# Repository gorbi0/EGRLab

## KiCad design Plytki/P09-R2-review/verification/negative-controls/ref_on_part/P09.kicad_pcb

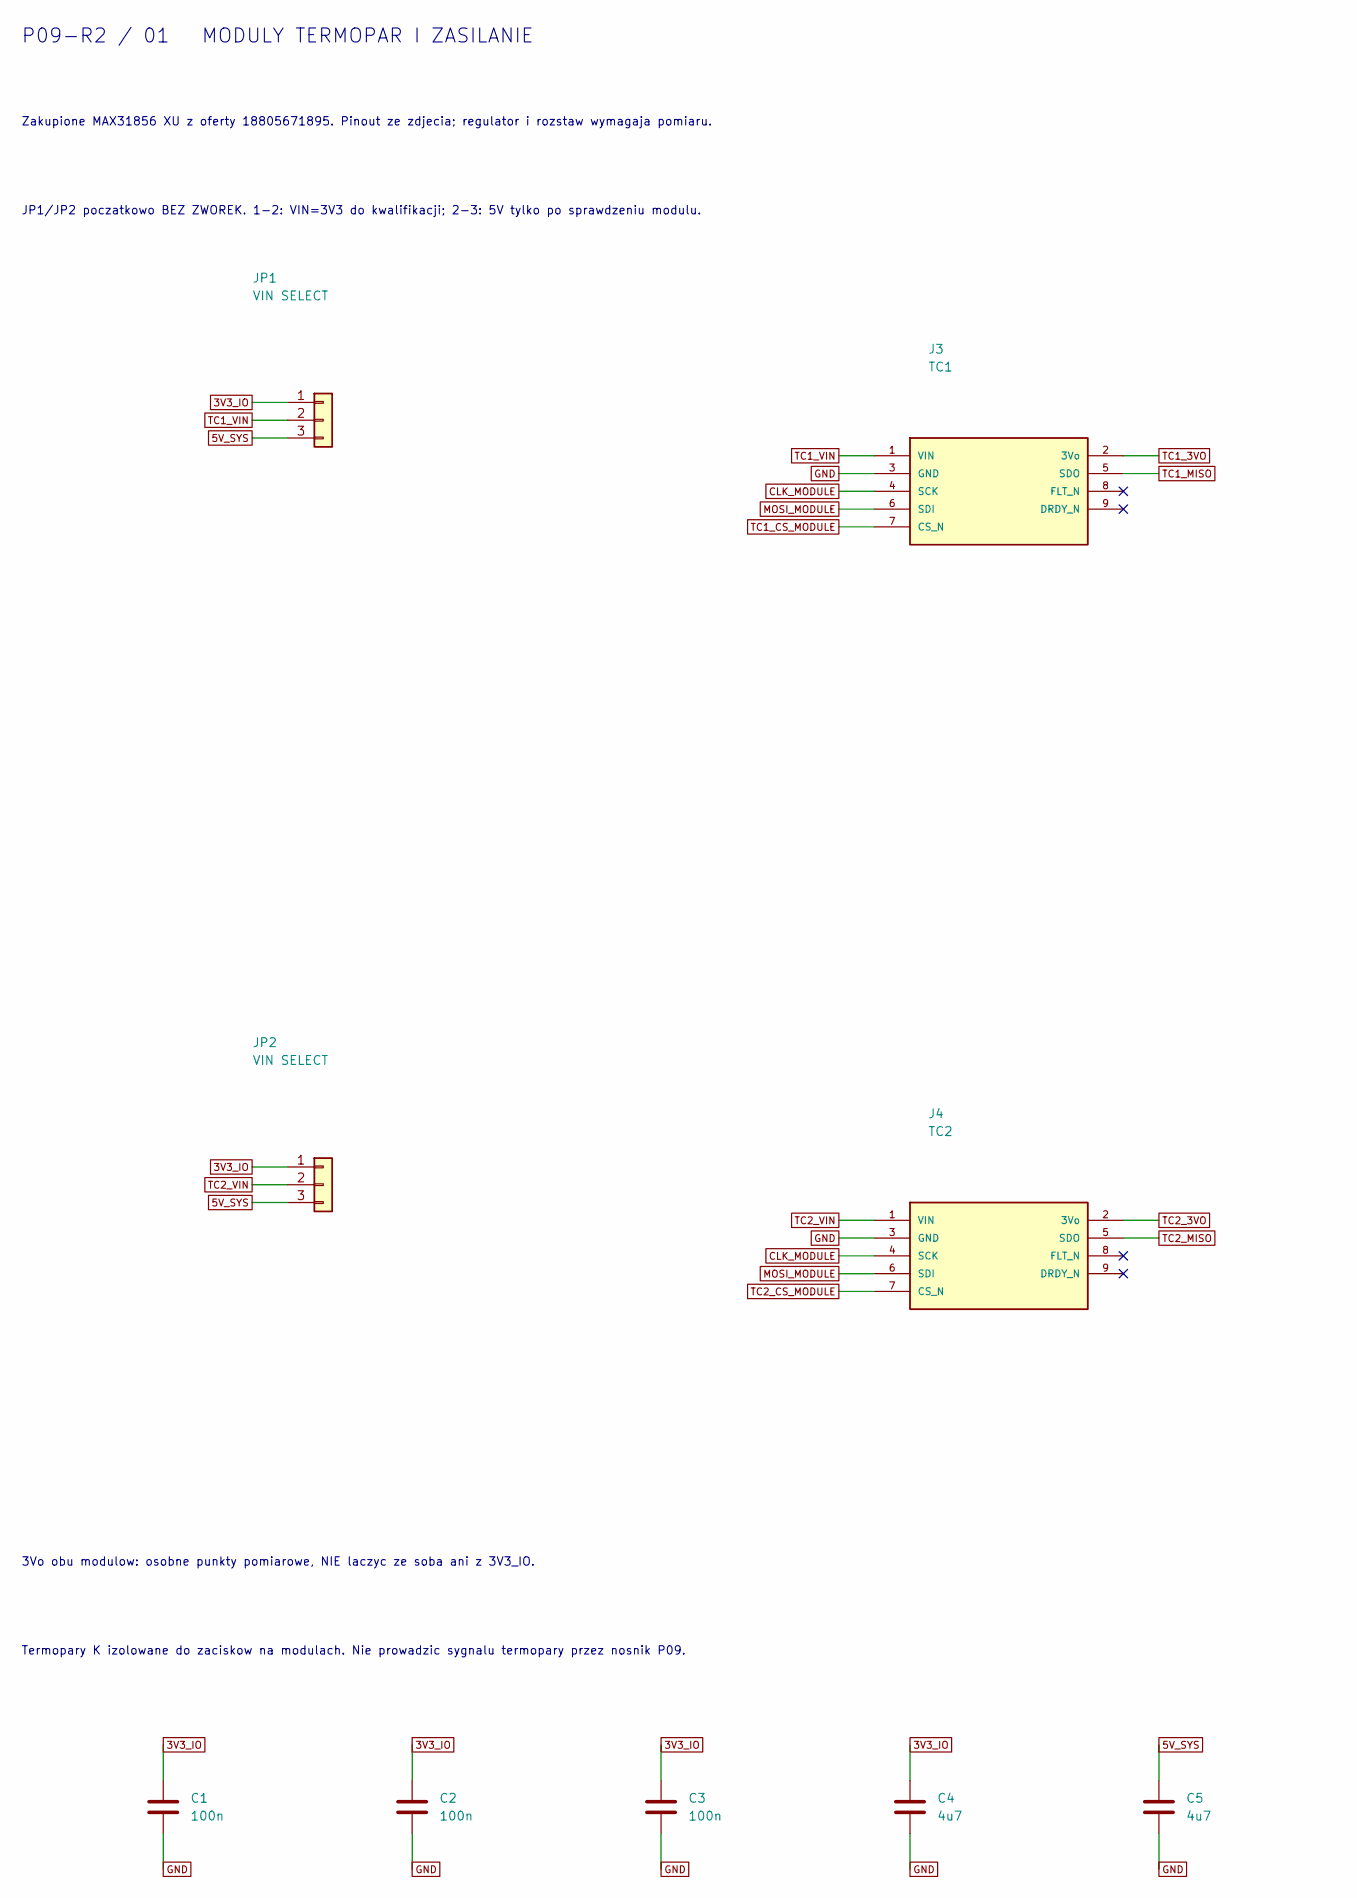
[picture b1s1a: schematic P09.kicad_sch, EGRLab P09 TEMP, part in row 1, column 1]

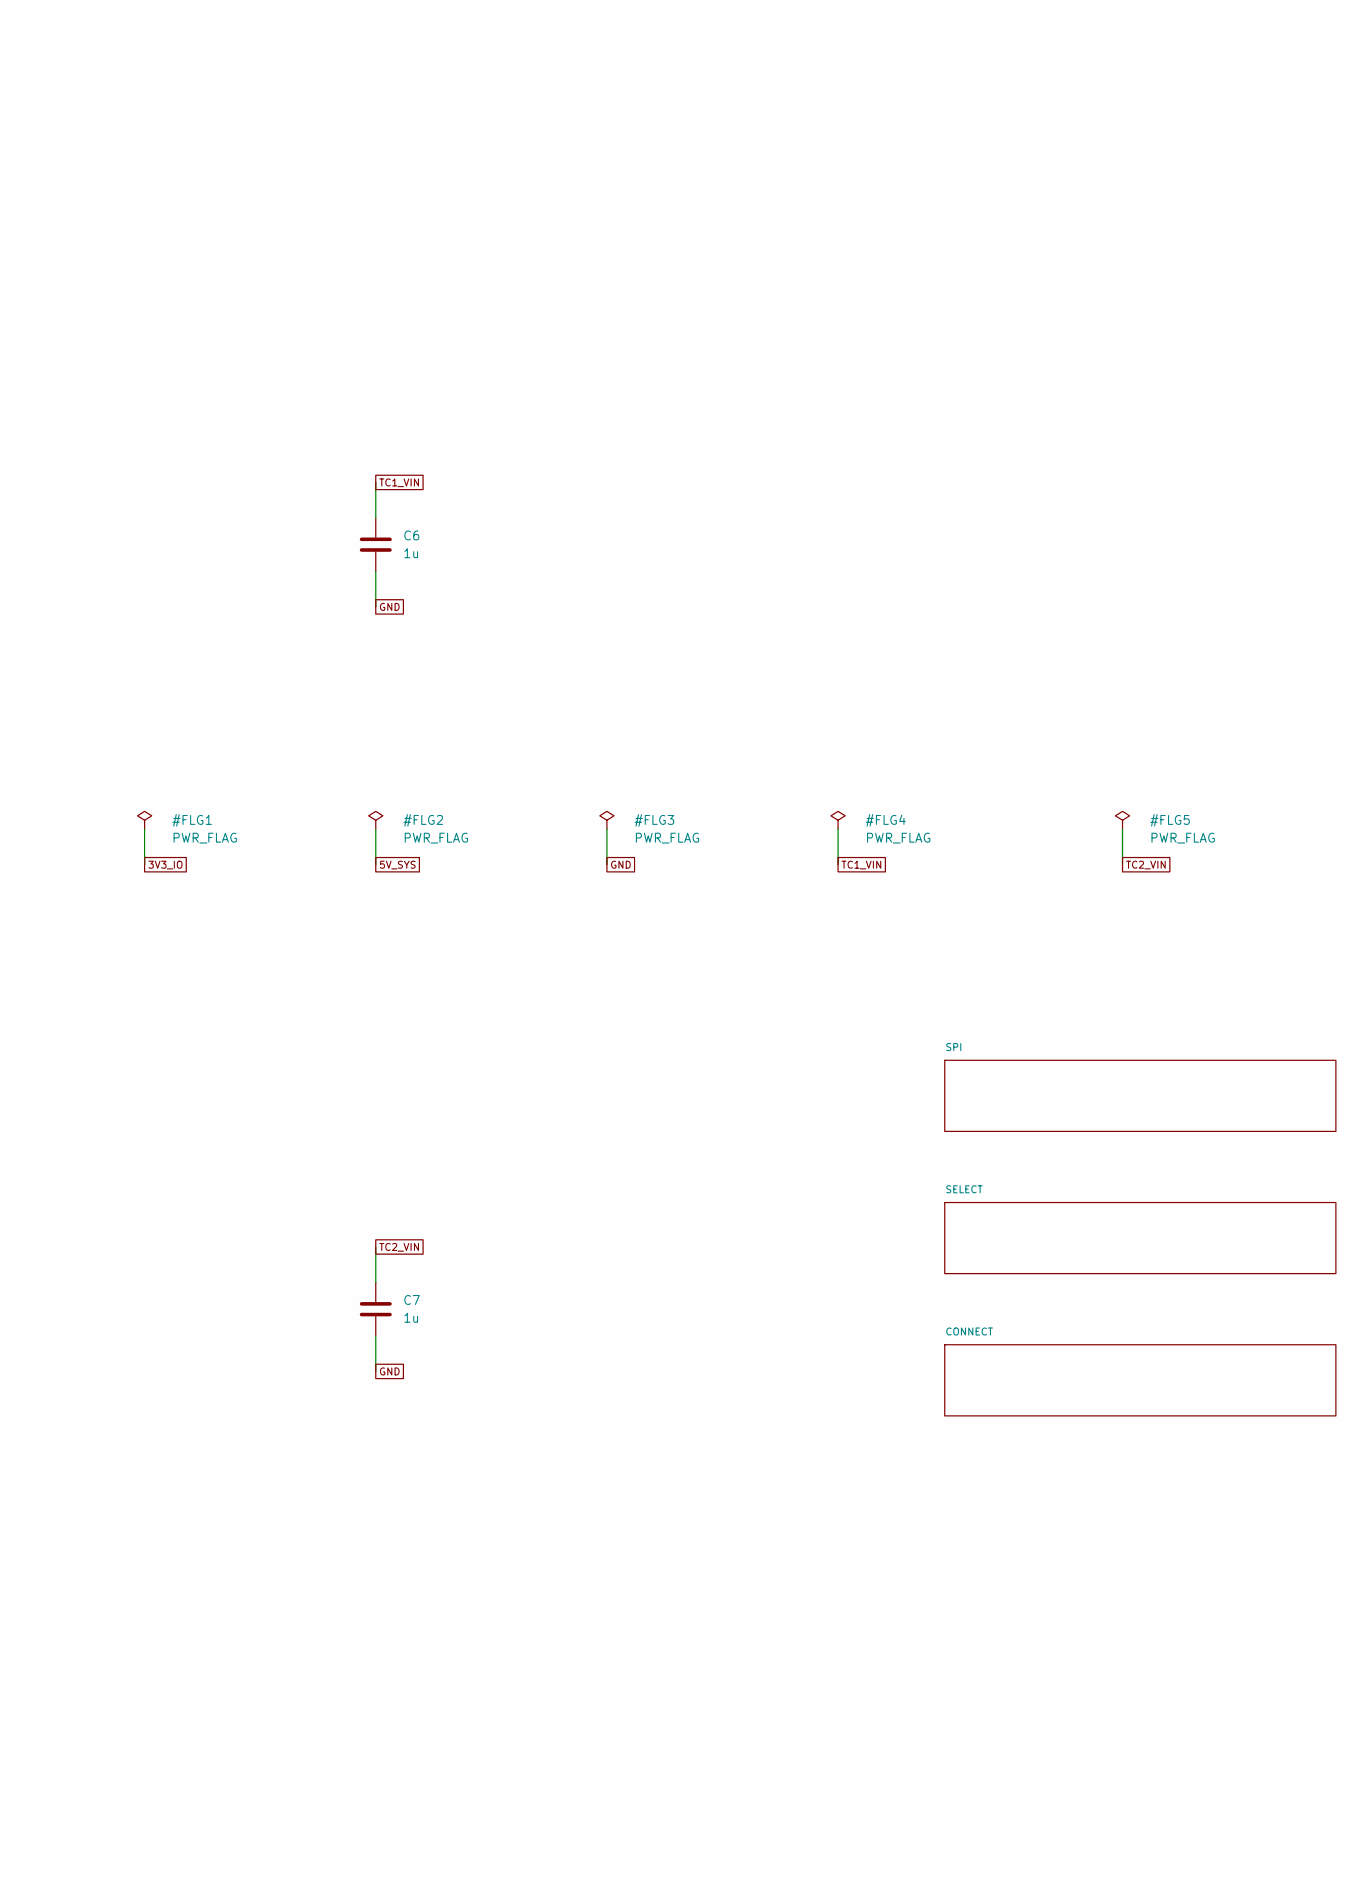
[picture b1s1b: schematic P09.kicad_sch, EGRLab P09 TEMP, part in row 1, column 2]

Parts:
C1, C2, C3: 100n; C_Disc_D5.0mm_W2.5mm_P5.00mm; MPN K104K15X7RF5TH5 Vishay 100n X7R 50V rad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
C4, C5: 4u7; C_1206_3216Metric_Pad1.33x1.80mm_HandSolder; MPN SMD 1206 X7R 25V 10% 4u7
C6, C7: 1u; C_1206_3216Metric_Pad1.33x1.80mm_HandSolder; MPN SMD 1206 X7R 25V 10% 1u
J3: TC1; MAX31856_XU_socket; MPN Socket 1x9 2.54mm Au + owned MAX31856 m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
J4: TC2; MAX31856_XU_socket; MPN Socket 1x9 2.54mm Au + owned MAX31856 m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
JP1, JP2: VIN SELECT; PinHeader_1x03_P2.54mm_Vertical; MPN Header 1x3 + one shunt (not fitted init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

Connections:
3V3_IO: C1.1, C2.1, C3.1, C4.1, JP1.1, JP2.1; also elsewhere on the board
5V_SYS: C5.1, JP1.3, JP2.3; also elsewhere on the board
CLK_MODULE: J3.4 (SCK), J4.4 (SCK); also elsewhere on the board
GND: C1.2, C2.2, C3.2, C4.2, C5.2, C6.2, C7.2, J3.3 (GND), J4.3 (GND); also elsewhere on the board
MOSI_MODULE: J3.6 (SDI), J4.6 (SDI); also elsewhere on the board
TC1_3VO: J3.2 (3Vo); also elsewhere on the board
TC1_CS_MODULE: J3.7 (CS_N); also elsewhere on the board
TC1_MISO: J3.5 (SDO); also elsewhere on the board
TC1_VIN: C6.1, J3.1 (VIN), JP1.2; also elsewhere on the board
TC2_3VO: J4.2 (3Vo); also elsewhere on the board
TC2_CS_MODULE: J4.7 (CS_N); also elsewhere on the board
TC2_MISO: J4.5 (SDO); also elsewhere on the board
TC2_VIN: C7.1, J4.1 (VIN), JP2.2; also elsewhere on the board

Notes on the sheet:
Zakupione MAX31856 XU z oferty 18805671895. Pinout ze zdjecia; regulator i rozstaw wymagaja pomiaru.
JP1/JP2 poczatkowo BEZ ZWOREK. 1-2: VIN=3V3 do kwalifikacji; 2-3: 5V tylko po sprawdzeniu modulu.
3Vo obu modulow: osobne punkty pomiarowe, NIE laczyc ze soba ani z 3V3_IO.
Termopary K izolowane do zaciskow na modulach. Nie prowadzic sygnalu termopary przez nosnik P09.
P09-R2 / 01 MODULY TERMOPAR I ZASILANIE

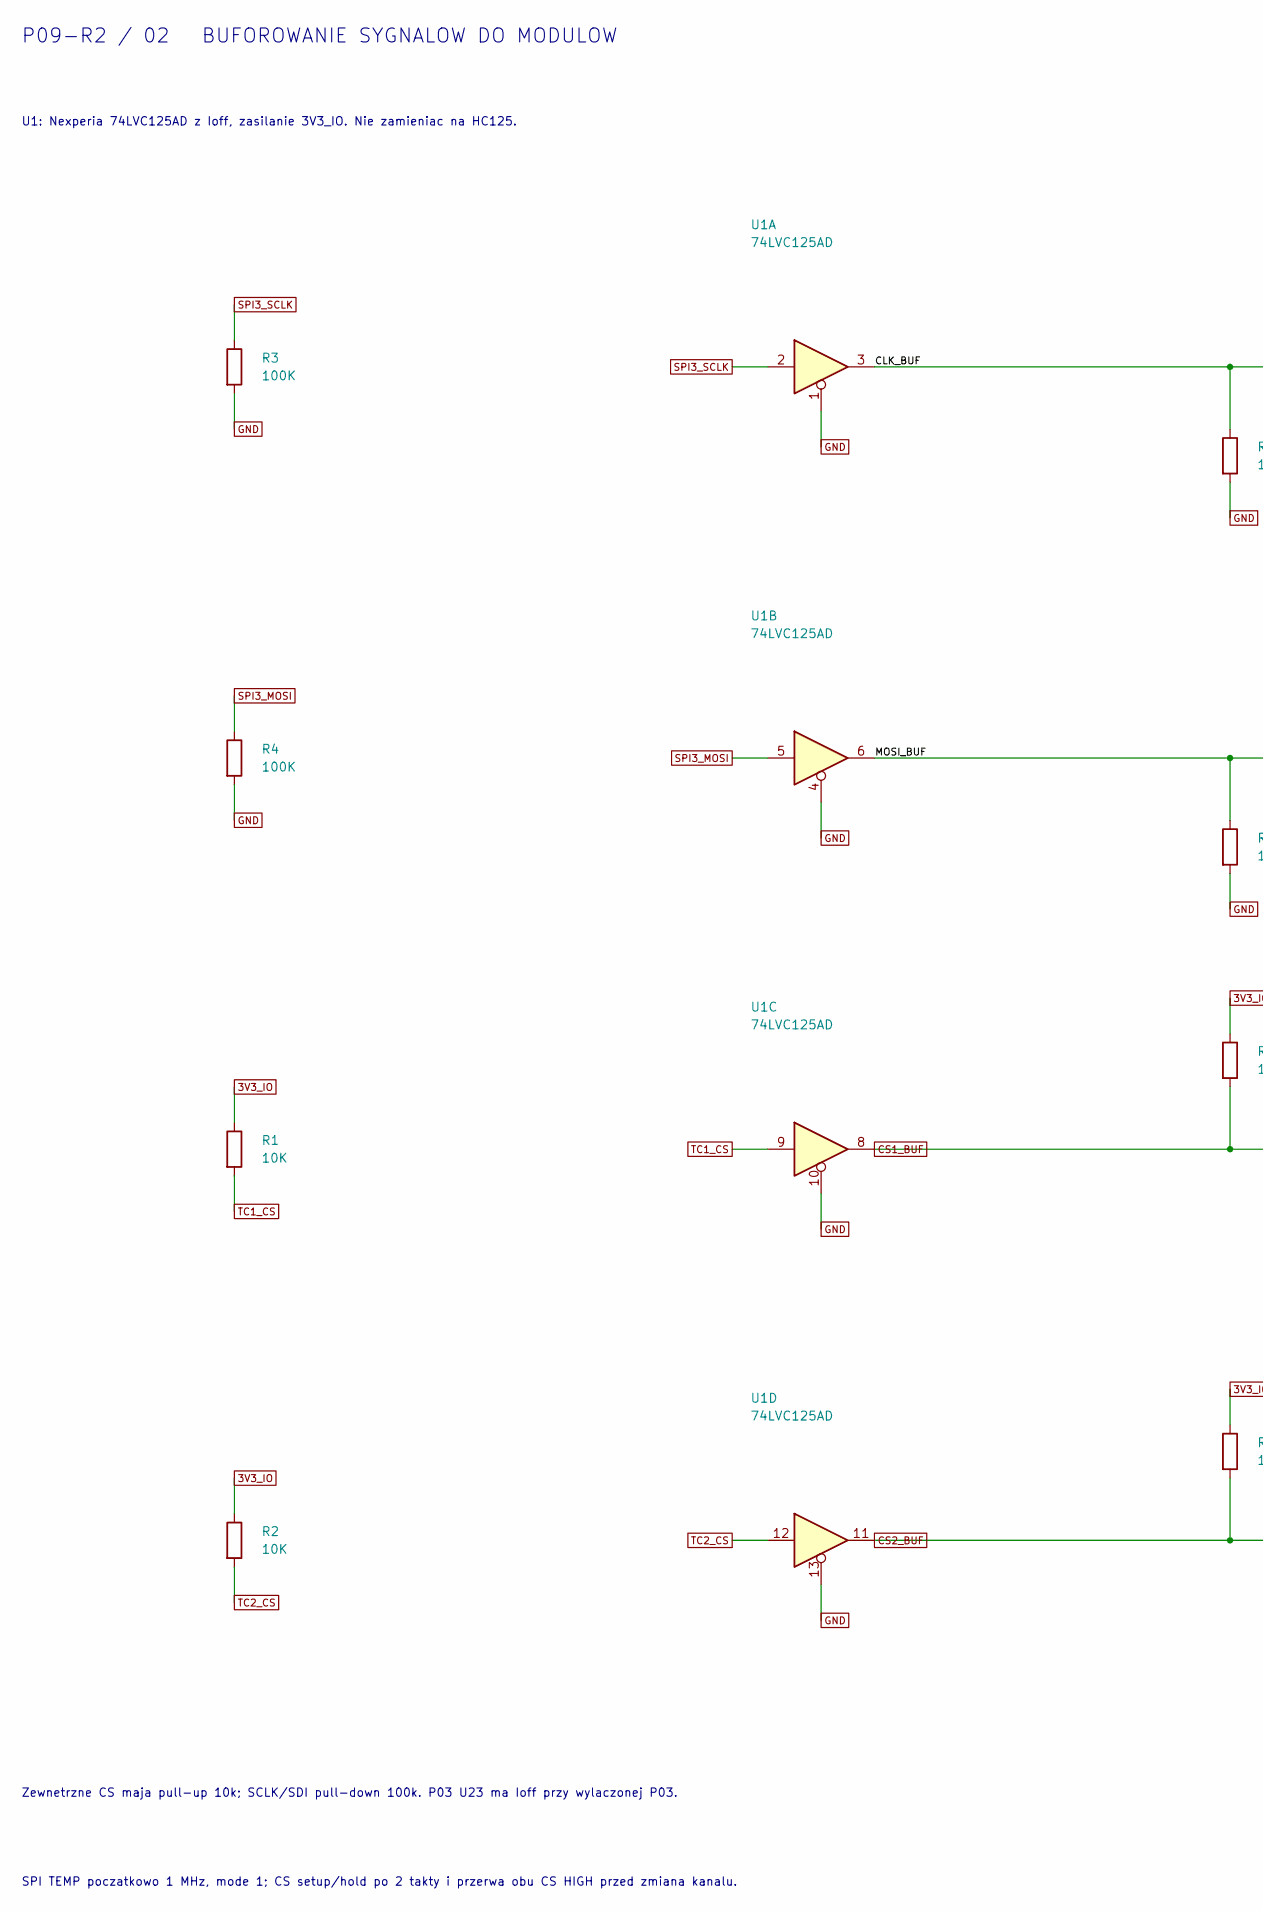
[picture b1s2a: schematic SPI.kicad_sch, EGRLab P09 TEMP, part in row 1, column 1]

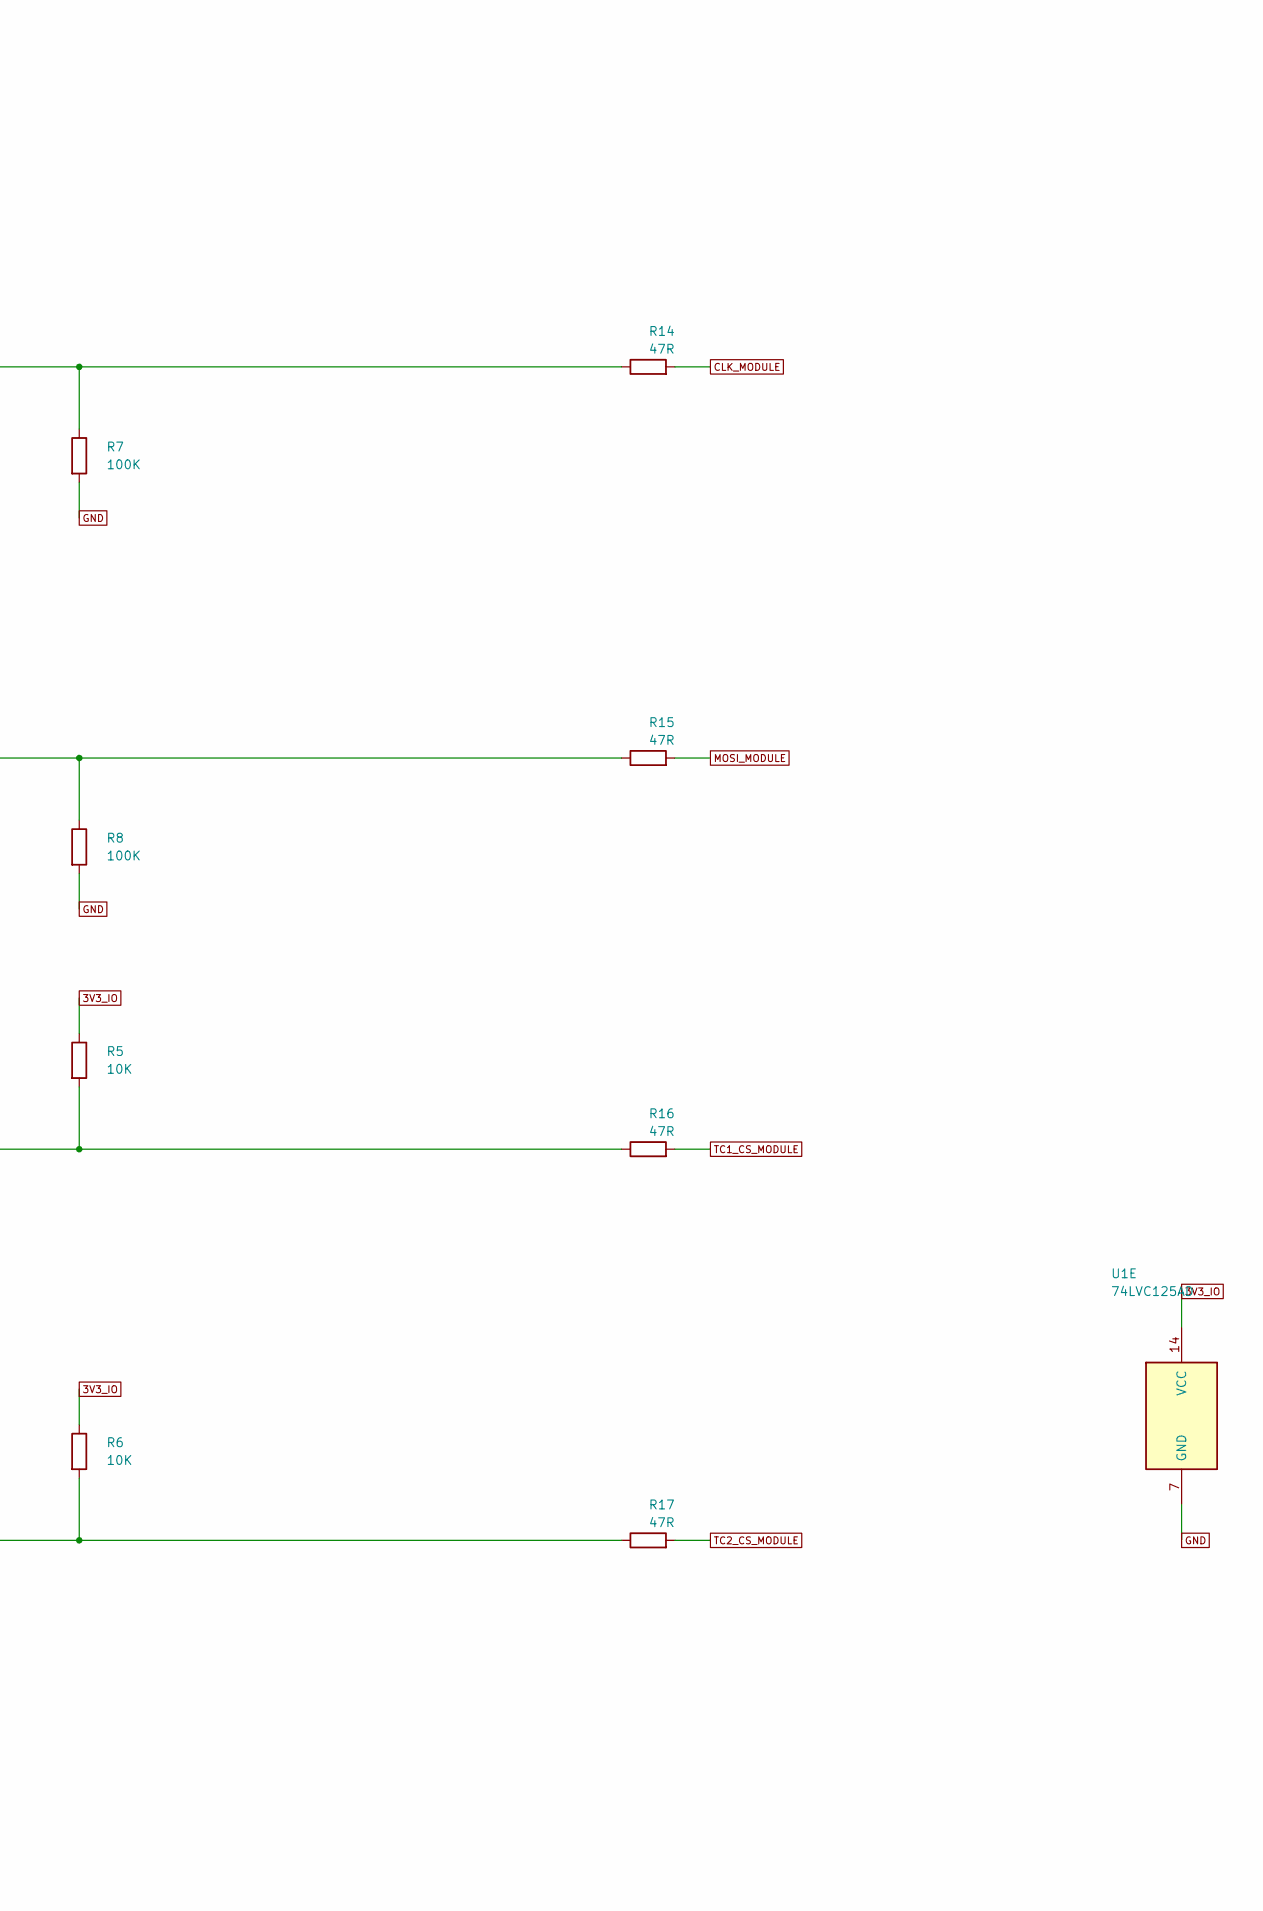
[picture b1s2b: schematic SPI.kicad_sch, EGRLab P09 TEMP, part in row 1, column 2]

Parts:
R1, R2, R5, R6: 10K; R_Axial_DIN0207_L6.3mm_D2.5mm_P5.08mm_Vertical; MPN MF0207 Yageo 10K 1% 0.6W (owned, standi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
R3, R4, R7, R8: 100K; R_Axial_DIN0207_L6.3mm_D2.5mm_P5.08mm_Vertical; MPN MF0207 Yageo 100K 1% 0.6W (owned, stand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
R14, R15, R16, R17: 47R; R_1206_3216Metric_Pad1.30x1.75mm_HandSolder; MPN SMD 1206 1% 0.25W 47R
U1: 74LVC125AD; SOIC-14_3.9x8.7mm_P1.27mm; MPN 74LVC125AD,118 Nexperia

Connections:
3V3_IO: R1.1, R2.1, R5.1, R6.1, U1.14 (VCC); also elsewhere on the board
/SPI/CLK_BUF: R7.1, R14.1, U1.3
/SPI/MOSI_BUF: R8.1, R15.1, U1.6
CLK_MODULE: R14.2; also elsewhere on the board
CS1_BUF: R5.2, R16.1, U1.8; also elsewhere on the board
CS2_BUF: R6.2, R17.1, U1.11; also elsewhere on the board
GND: R3.2, R4.2, R7.2, R8.2, U1.1, U1.4, U1.7 (GND), U1.10, U1.13; also elsewhere on the board
MOSI_MODULE: R15.2; also elsewhere on the board
SPI3_MOSI: R4.1, U1.5; also elsewhere on the board
SPI3_SCLK: R3.1, U1.2; also elsewhere on the board
TC1_CS: R1.2, U1.9; also elsewhere on the board
TC1_CS_MODULE: R16.2; also elsewhere on the board
TC2_CS: R2.2, U1.12; also elsewhere on the board
TC2_CS_MODULE: R17.2; also elsewhere on the board

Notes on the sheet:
U1: Nexperia 74LVC125AD z Ioff, zasilanie 3V3_IO. Nie zamieniac na HC125.
Zewnetrzne CS maja pull-up 10k; SCLK/SDI pull-down 100k. P03 U23 ma Ioff przy wylaczonej P03.
SPI TEMP poczatkowo 1 MHz, mode 1; CS setup/hold po 2 takty i przerwa obu CS HIGH przed zmiana kanalu.
P09-R2 / 02 BUFOROWANIE SYGNALOW DO MODULOW

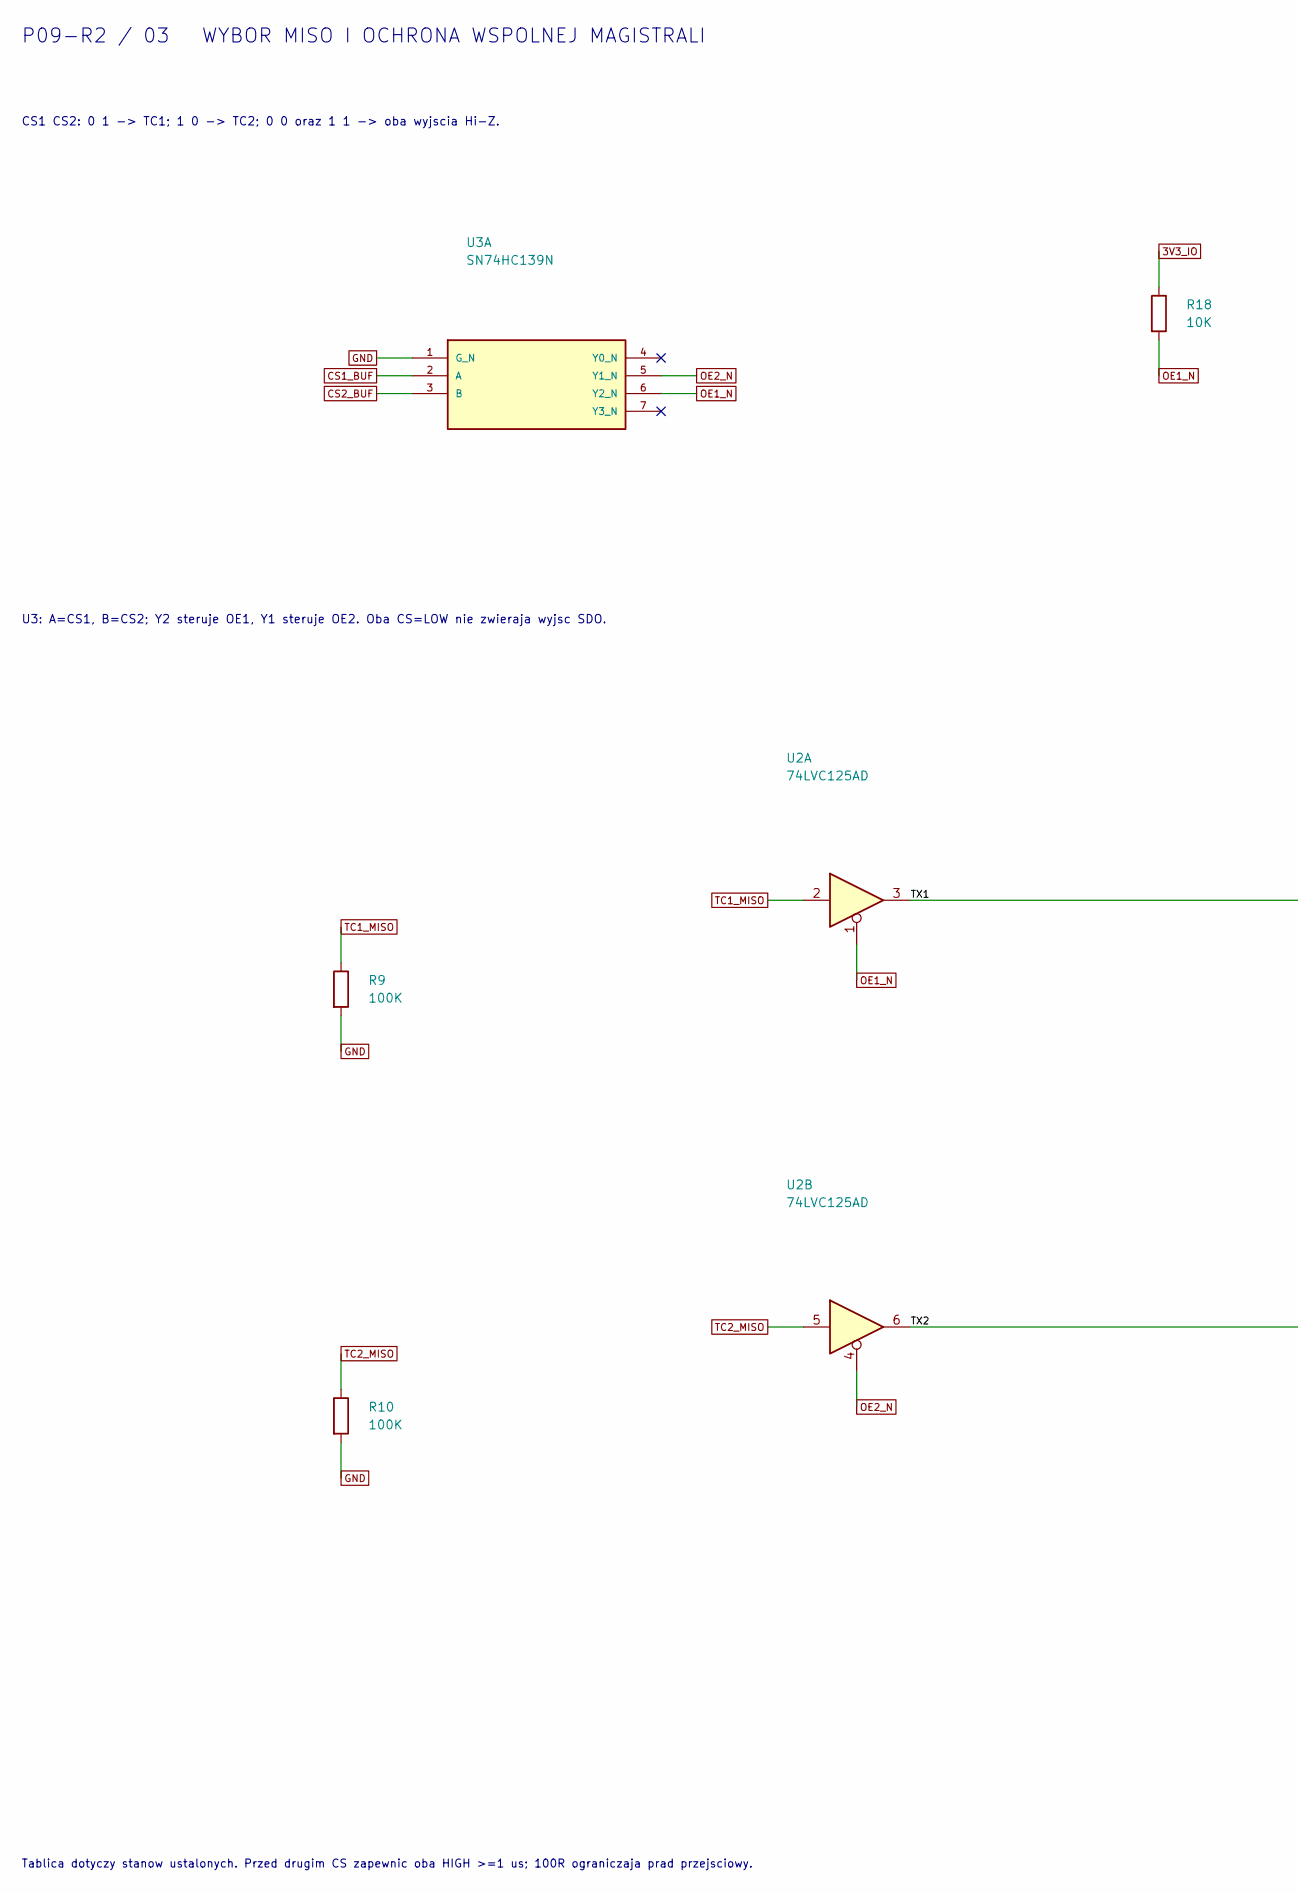
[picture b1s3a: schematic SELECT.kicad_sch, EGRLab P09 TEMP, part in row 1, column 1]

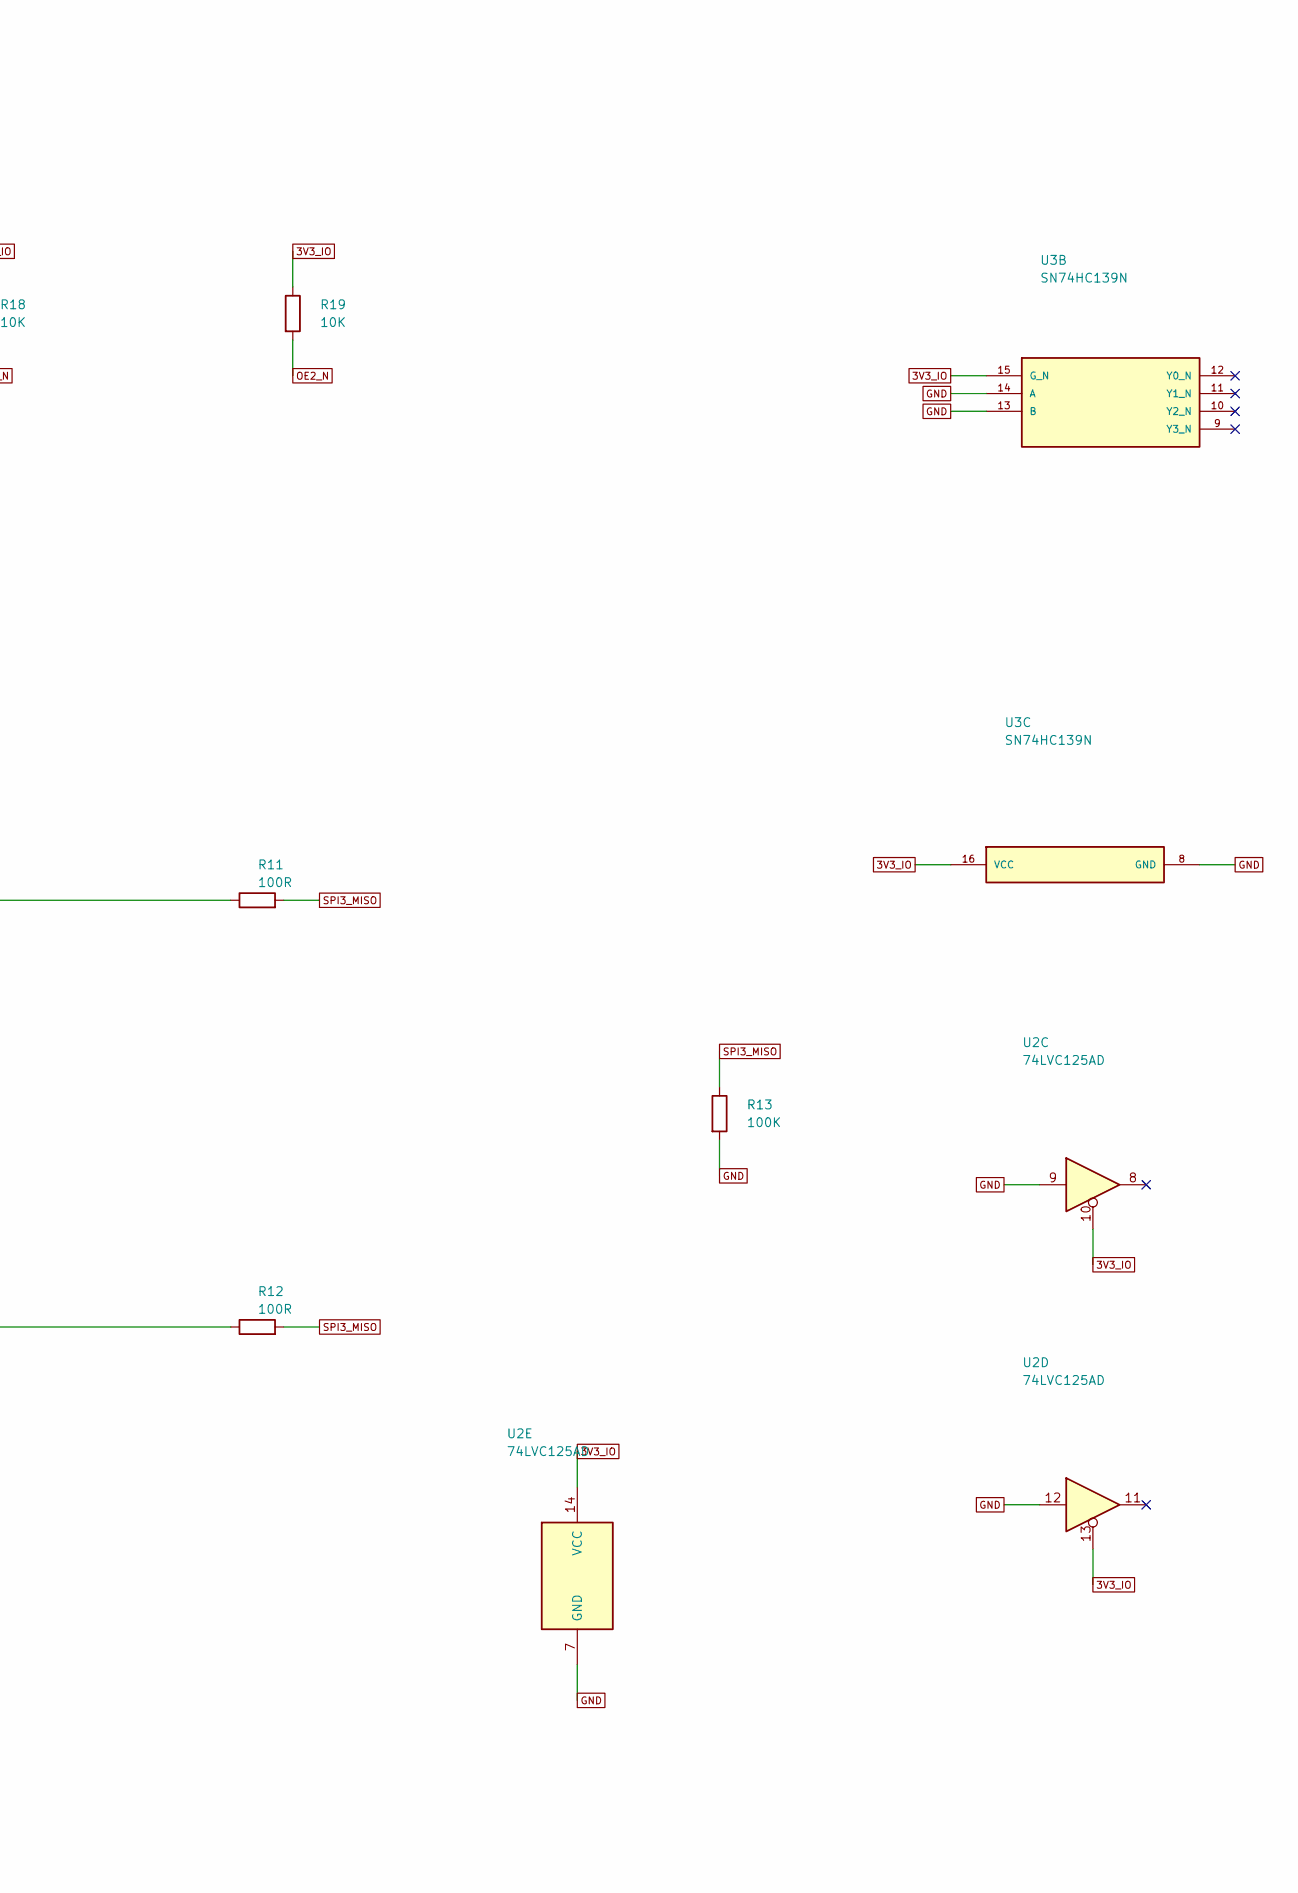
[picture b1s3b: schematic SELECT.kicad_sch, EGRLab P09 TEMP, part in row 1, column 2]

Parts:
R9, R10, R13: 100K; R_Axial_DIN0207_L6.3mm_D2.5mm_P5.08mm_Vertical; MPN MF0207 Yageo 100K 1% 0.6W (owned, stand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
R11, R12: 100R; R_1206_3216Metric_Pad1.30x1.75mm_HandSolder; MPN SMD 1206 1% 0.25W 100R
R18, R19: 10K; R_Axial_DIN0207_L6.3mm_D2.5mm_P5.08mm_Vertical; MPN MF0207 Yageo 10K 1% 0.6W (owned, standi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
U2: 74LVC125AD; SOIC-14_3.9x8.7mm_P1.27mm; MPN 74LVC125AD,118 Nexperia
U3: SN74HC139N; DIP-16_W7.62mm; MPN SN74HC139N

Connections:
3V3_IO: R18.1, R19.1, U2.10, U2.13, U2.14 (VCC), U3.15 (G_N), U3.16 (VCC); also elsewhere on the board
/SELECT/TX1: R11.1, U2.3
/SELECT/TX2: R12.1, U2.6
CS1_BUF: U3.2 (A); also elsewhere on the board
CS2_BUF: U3.3 (B); also elsewhere on the board
GND: R9.2, R10.2, R13.2, U2.7 (GND), U2.9, U2.12, U3.1 (G_N), U3.8 (GND), U3.13 (B), U3.14 (A); also elsewhere on the board
OE1_N: R18.2, U2.1, U3.6 (Y2_N); also elsewhere on the board
OE2_N: R19.2, U2.4, U3.5 (Y1_N); also elsewhere on the board
SPI3_MISO: R11.2, R12.2, R13.1; also elsewhere on the board
TC1_MISO: R9.1, U2.2; also elsewhere on the board
TC2_MISO: R10.1, U2.5; also elsewhere on the board

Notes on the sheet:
CS1 CS2: 0 1 -> TC1; 1 0 -> TC2; 0 0 oraz 1 1 -> oba wyjscia Hi-Z.
U3: A=CS1, B=CS2; Y2 steruje OE1, Y1 steruje OE2. Oba CS=LOW nie zwieraja wyjsc SDO.
Tablica dotyczy stanow ustalonych. Przed drugim CS zapewnic oba HIGH >=1 us; 100R ograniczaja prad przejsciowy.
P09-R2 / 03 WYBOR MISO I OCHRONA WSPOLNEJ MAGISTRALI

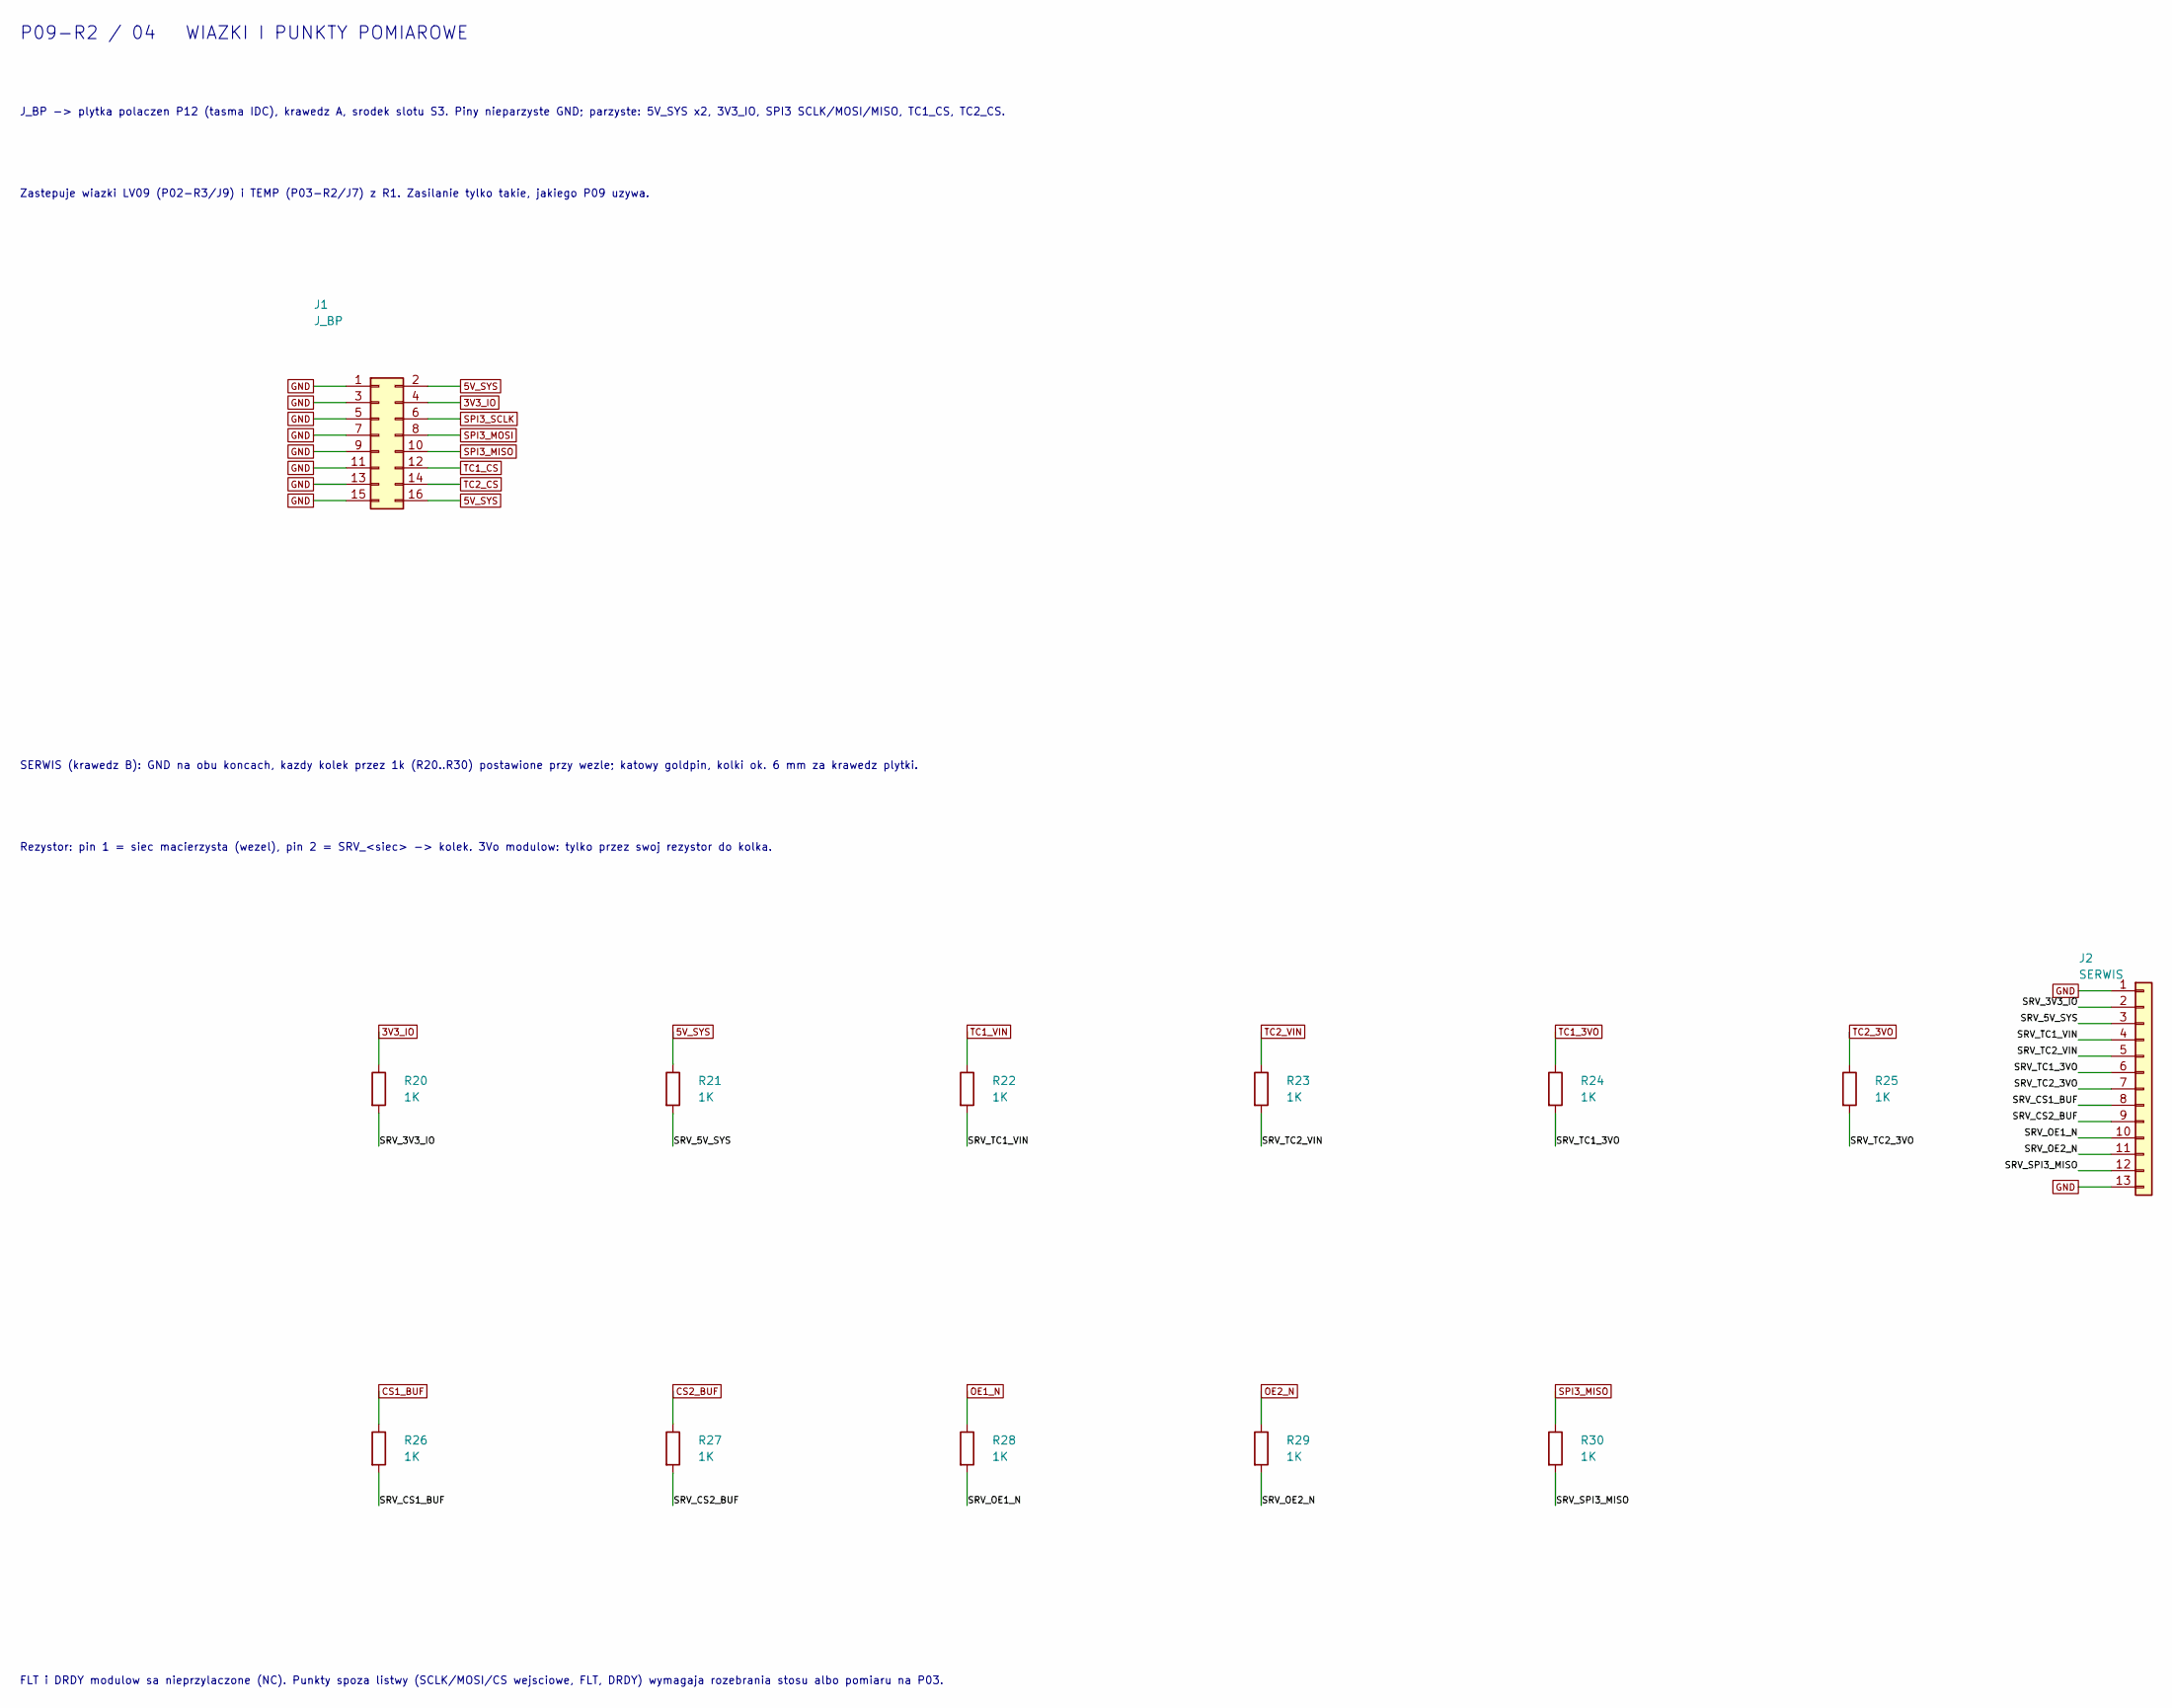
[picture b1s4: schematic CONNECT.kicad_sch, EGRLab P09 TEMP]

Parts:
J1: J_BP; IDC-Header_2x08_P2.54mm_Horizontal; MPN IDC header 2x8 2.54mm angled shrouded, 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
J2: SERWIS; PinHeader_1x13_P2.54mm_Horizontal; MPN Goldpin 1x13 2.54mm angled (buy angled 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
R20, R21, R22, R23, R24, R25, R26, R27, R28, R29, R30: 1K; R_1206_3216Metric_Pad1.30x1.75mm_HandSolder; MPN SMD 1206 1% 0.25W 1K

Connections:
3V3_IO: J1.4, R20.1; also elsewhere on the board
5V_SYS: J1.2, J1.16, R21.1; also elsewhere on the board
/CONNECT/SRV_3V3_IO: J2.2, R20.2
/CONNECT/SRV_5V_SYS: J2.3, R21.2
/CONNECT/SRV_CS1_BUF: J2.8, R26.2
/CONNECT/SRV_CS2_BUF: J2.9, R27.2
/CONNECT/SRV_OE1_N: J2.10, R28.2
/CONNECT/SRV_OE2_N: J2.11, R29.2
/CONNECT/SRV_SPI3_MISO: J2.12, R30.2
/CONNECT/SRV_TC1_3VO: J2.6, R24.2
/CONNECT/SRV_TC1_VIN: J2.4, R22.2
/CONNECT/SRV_TC2_3VO: J2.7, R25.2
/CONNECT/SRV_TC2_VIN: J2.5, R23.2
CS1_BUF: R26.1; also elsewhere on the board
CS2_BUF: R27.1; also elsewhere on the board
GND: J1.1, J1.3, J1.5, J1.7, J1.9, J1.11, J1.13, J1.15, J2.1, J2.13; also elsewhere on the board
OE1_N: R28.1; also elsewhere on the board
OE2_N: R29.1; also elsewhere on the board
SPI3_MISO: J1.10, R30.1; also elsewhere on the board
SPI3_MOSI: J1.8; also elsewhere on the board
SPI3_SCLK: J1.6; also elsewhere on the board
TC1_3VO: R24.1; also elsewhere on the board
TC1_CS: J1.12; also elsewhere on the board
TC1_VIN: R22.1; also elsewhere on the board
TC2_3VO: R25.1; also elsewhere on the board
TC2_CS: J1.14; also elsewhere on the board
TC2_VIN: R23.1; also elsewhere on the board

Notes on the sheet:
J_BP -> plytka polaczen P12 (tasma IDC), krawedz A, srodek slotu S3. Piny nieparzyste GND; parzyste: 5V_SYS x2, 3V3_IO, SPI3 SCLK/MOSI/MISO, TC1_CS, TC2_CS.
Zastepuje wiazki LV09 (P02-R3/J9) i TEMP (P03-R2/J7) z R1. Zasilanie tylko takie, jakiego P09 uzywa.
SERWIS (krawedz B): GND na obu koncach, kazdy kolek przez 1k (R20..R30) postawione przy wezle; katowy goldpin, kolki ok. 6 mm za krawedz plytki.
Rezystor: pin 1 = siec macierzysta (wezel), pin 2 = SRV_<siec> -> kolek. 3Vo modulow: tylko przez swoj rezystor do kolka.
FLT i DRDY modulow sa nieprzylaczone (NC). Punkty spoza listwy (SCLK/MOSI/CS wejsciowe, FLT, DRDY) wymagaja rozebrania stosu albo pomiaru na P03.
P09-R2 / 04 WIAZKI I PUNKTY POMIAROWE
